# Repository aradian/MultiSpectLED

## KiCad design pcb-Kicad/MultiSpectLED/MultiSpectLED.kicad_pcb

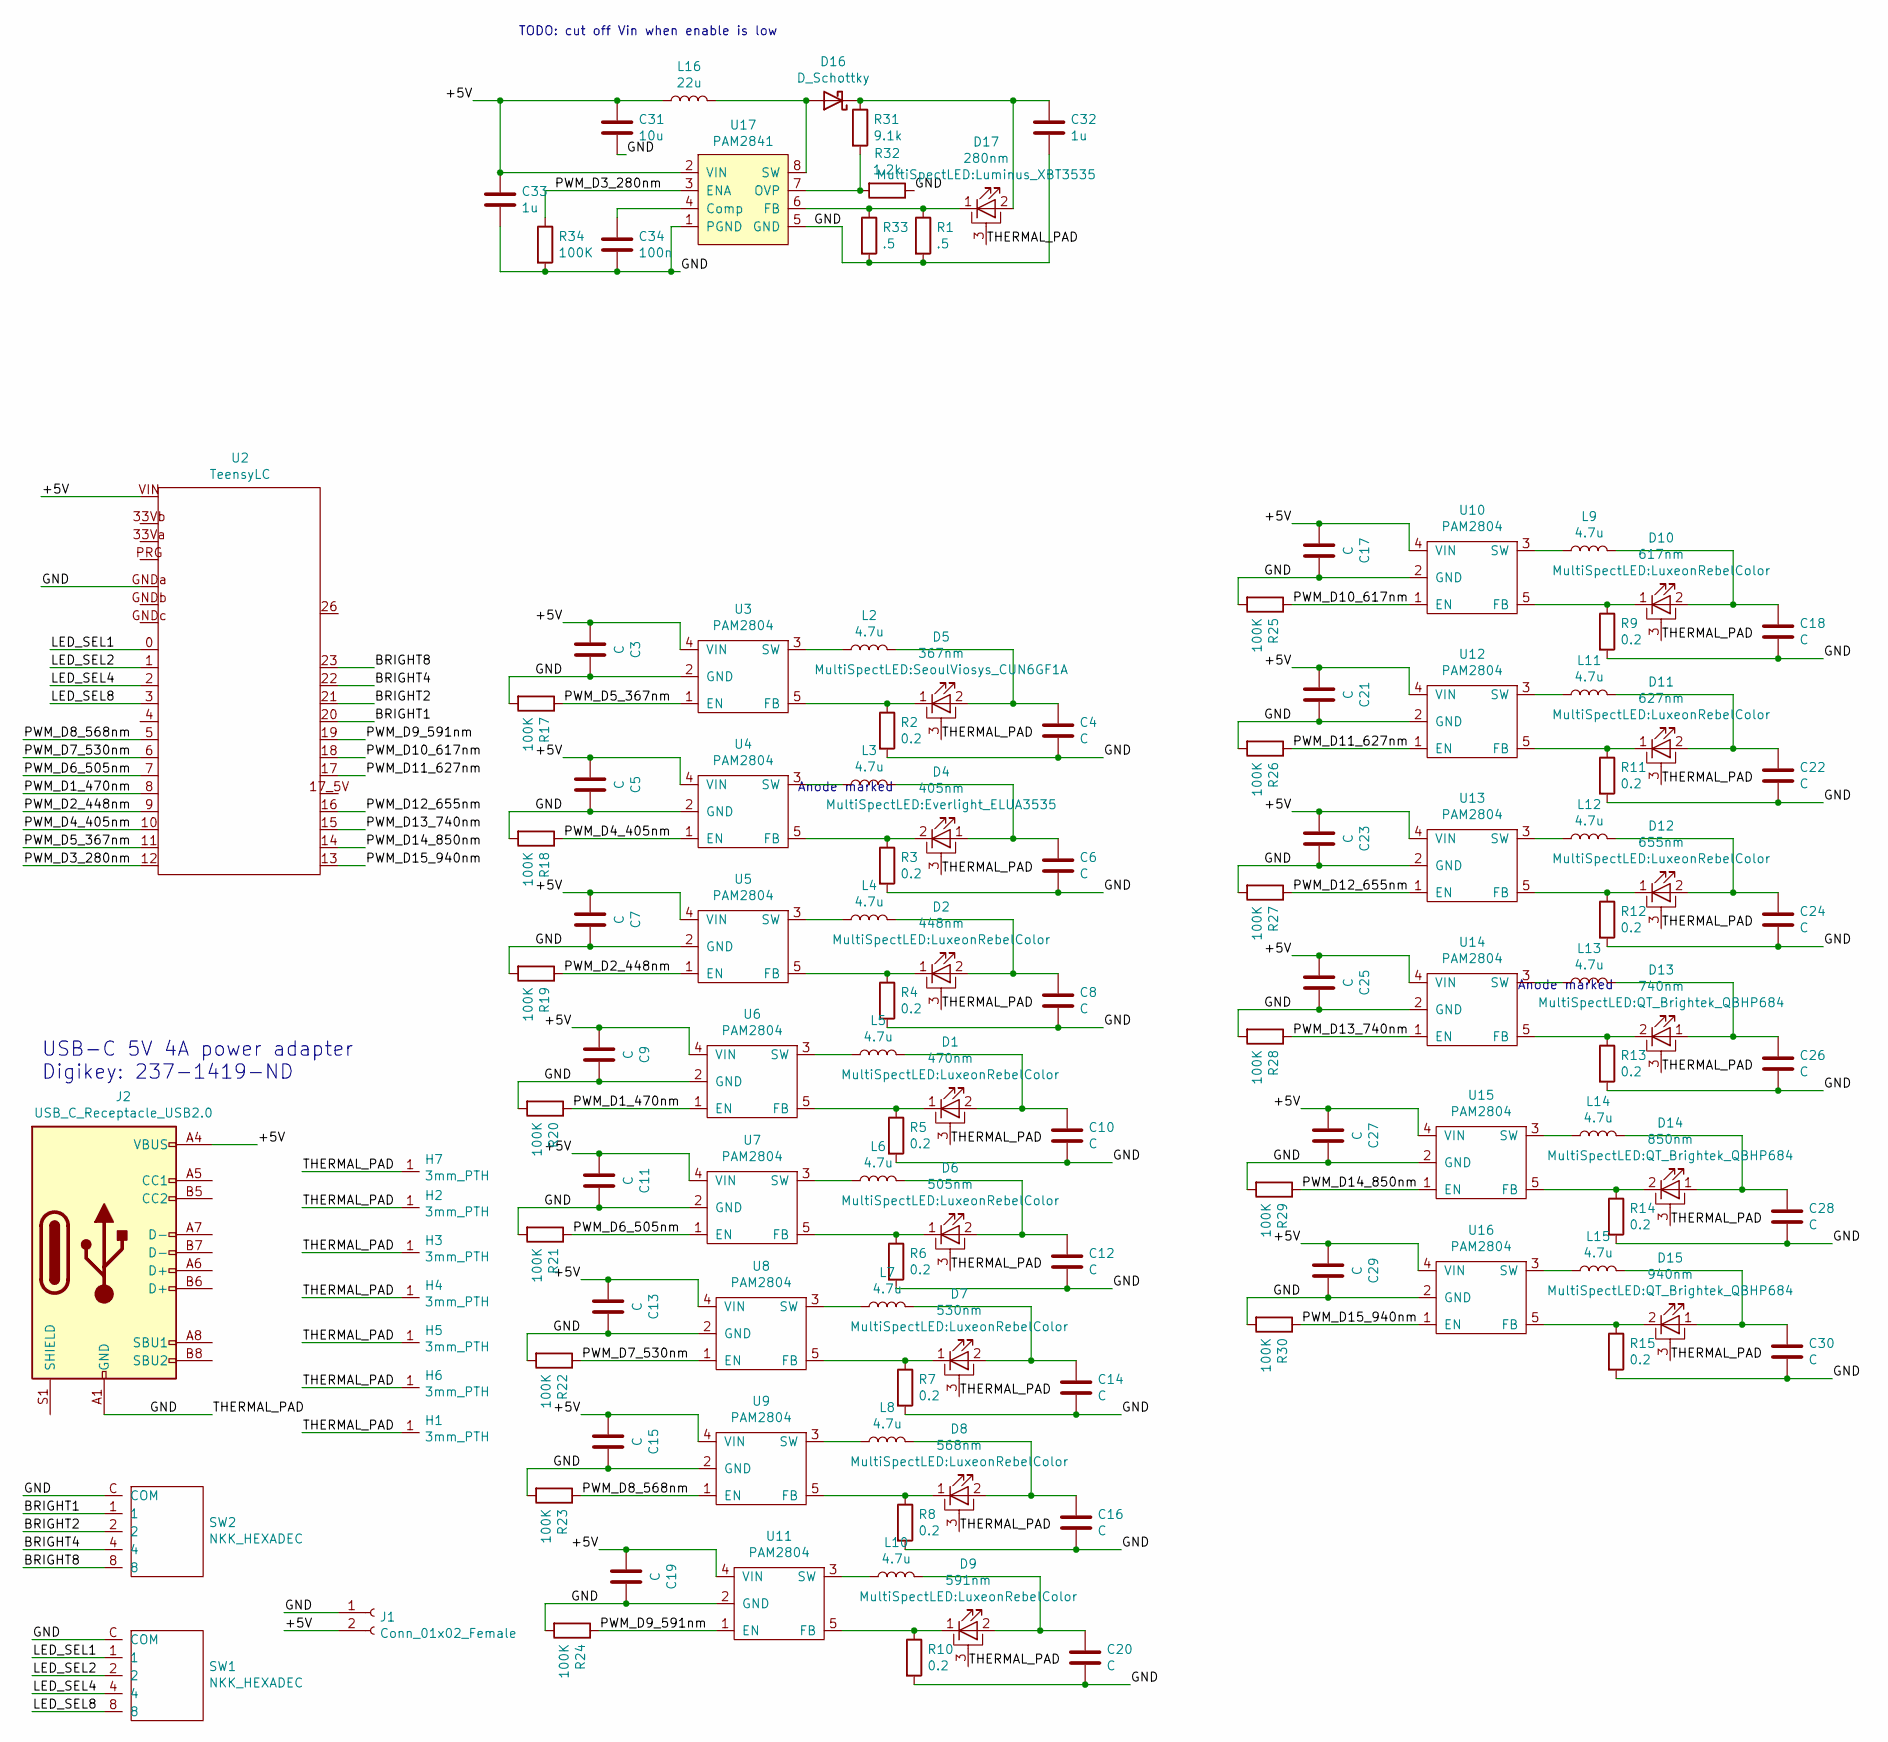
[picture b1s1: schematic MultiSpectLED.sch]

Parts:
C3, C4, C5, C6, C7, C8, C9, C10, C11, C12, C13, C14, C15, C16, C17, C18, C19, C20, C21, C22, C23, C24, C25, C26, C27, C28, C29, C30: C; C_0805_2012Metric; Digikey Part Number 490-3886-1-ND
C31: 10u; C_0805_2012Metric; Digi-Key_PN 1276-2891-1-ND
C32, C33: 1u; C_0805_2012Metric; Digi-Key_PN 1276-1066-1-ND
C34: 100n; C_0402_1005Metric; Digi-Key_PN 1276-1043-1-ND
D1: 470nm; LuxeonRebelColor; Digikey Part Number 1416-1029-1-ND
D2: 448nm; LuxeonRebelColor; Digikey Part Number 1416-1038-1-ND
D4: 405nm; Everlight_ELUA3535; Digikey Part Number 1080-1620-1-ND
D5: 367nm; SeoulViosys_CUN6GF1A; Digikey Part Number 2112-CUN6GF1ACT-ND
D6: 505nm; LuxeonRebelColor; Digikey Part Number 1416-1031-1-ND
D7: 530nm; LuxeonRebelColor; Digikey Part Number 1416-1036-1-ND
D8: 568nm; LuxeonRebelColor; Digikey Part Number 1416-1185-1-ND
D9: 591nm; LuxeonRebelColor; Digikey Part Number 1416-1027-1-ND
D10: 617nm; LuxeonRebelColor; Digikey Part Number 1416-1026-1-ND
D11: 627nm; LuxeonRebelColor; Digikey Part Number 1416-1024-1-ND
D12: 655nm; LuxeonRebelColor; Digikey Part Number 1416-1701-1-ND
D13: 740nm; QT_Brightek_QBHP684; Digikey Part Number 1516-1213-1-ND
D14: 850nm; QT_Brightek_QBHP684
D15: 940nm; QT_Brightek_QBHP684
D16: D_Schottky; D_TUMD2; Digi-Key_PN MSS2P2-M3/89AGICT-ND
D17: 280nm; Luminus_XBT3535; Digikey Part Number 1214-XBT-3535-UV-A130-CD270-00CT-ND
H1, H2, H3, H4, H5, H6, H7: 3mm_PTH
J1: Conn_01x02_Female; FAN_PADS
J2: USB_C_Receptacle_USB2.0; USB_C_Receptacle_Amphenol_12401610E4-2A; Digikey Part Number 12401610E4#2ACT-ND
L2, L3, L4, L5, L6, L7, L8, L9, L10, L11, L12, L13, L14, L15: 4.7u; L_1007_2518Metric; Digikey Part Number 587-1621-1-ND
L16: 22u; L_Taiyo-Yuden_NR-50xx; Digikey Part Number 587-NRS5040T220MMGKCT-ND
R1, R33: .5; R_0603_1608Metric; Digi-Key_PN CSR0603FKR500CT-ND
R2, R3, R4, R5, R6, R7, R8, R9, R10, R11, R12, R13, R14, R15: 0.2; R_0805_2012Metric; Digikey Part Number RL12S.20FCT-ND
R17, R18, R19, R20, R21, R22, R23, R24, R25, R26, R27, R28, R29, R30, R34: 100K; R_0402_1005Metric; Digikey Part Number RC1005F104CS
R31: 9.1k; R_0402_1005Metric; Digi-Key_PN RMCF0402FT9K10CT-ND
R32: 1.2k; R_0402_1005Metric; Digi-Key_PN RMCF0402FT1K20CT-ND
SW1, SW2: NKK_HEXADEC; NKK_FR02; Digikey Part Number 360-2543-1-ND
U2: TeensyLC; Digikey Part Number 1568-1233-ND
U3, U4, U5, U6, U7, U8, U9, U10, U11, U12, U13, U14, U15, U16: PAM2804; SOT-23-5; Digikey Part Number PAM2804AAB010DICT-ND
U17: PAM2841; MSOP-8_3x3mm_P0.65mm

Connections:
/+5V: C3.2, C5.2, C7.2, C9.2, C11.2, C13.2, C15.2, C17.2, C19.2, C21.2, C23.2, C25.2, C27.2, C29.2, C31.2, C33.1, J1.2, J2.A4 (VBUS), J2.A9 (VBUS), J2.B4 (VBUS), J2.B9 (VBUS), L16.1, U2.VIN, U3.4 (VIN), U4.4 (VIN), U5.4 (VIN), U6.4 (VIN), U7.4 (VIN), U8.4 (VIN), U9.4 (VIN), U10.4 (VIN), U11.4 (VIN), U12.4 (VIN), U13.4 (VIN), U14.4 (VIN), U15.4 (VIN), U16.4 (VIN), U17.2 (VIN)
/BRIGHT1: SW2.1, U2.20
/BRIGHT2: SW2.2, U2.21
/BRIGHT4: SW2.4, U2.22
/BRIGHT8: SW2.8, U2.23
/GND: C3.1, C4.2, C5.1, C6.2, C7.1, C8.2, C9.1, C10.2, C11.1, C12.2, C13.1, C14.2, C15.1, C16.2, C17.1, C18.2, C19.1, C20.2, C21.1, C22.2, C23.1, C24.2, C25.1, C26.2, C27.1, C28.2, C29.1, C30.2, C31.1, C32.2, C33.2, C34.2, D1.3 (PAD), D2.3 (PAD), D4.3 (PAD), D5.3 (PAD), D6.3 (PAD), D7.3 (PAD), D8.3 (PAD), D9.3 (PAD), D10.3 (PAD), D11.3 (PAD), D12.3 (PAD), D13.3 (PAD), D14.3 (PAD), D15.3 (PAD), D17.3 (PAD), H1.1, H2.1, H3.1, H4.1, H5.1, H6.1, H7.1, J1.1, J2.A1 (GND), J2.A12 (GND), J2.B1 (GND), J2.B12 (GND), R1.2, R2.2, R3.2, R4.2, R5.2, R6.2, R7.2, R8.2, R9.2, R10.2, R11.2, R12.2, R13.2, R14.2, R15.2, R17.2, R18.2, R19.2, R20.2, R21.2, R22.2, R23.2, R24.2, R25.2, R26.2, R27.2, R28.2, R29.2, R30.2, R32.1, R33.2, R34.2, SW1.C (COM), SW2.C (COM), U2.GNDa, U3.2 (GND), U4.2 (GND), U5.2 (GND), U6.2 (GND), U7.2 (GND), U8.2 (GND), U9.2 (GND), U10.2 (GND), U11.2 (GND), U12.2 (GND), U13.2 (GND), U14.2 (GND), U15.2 (GND), U16.2 (GND), U17.1 (PGND), U17.5 (GND)
/LED_SEL1: SW1.1, U2.0
/LED_SEL2: SW1.2, U2.1
/LED_SEL4: SW1.4, U2.2
/LED_SEL8: SW1.8, U2.3
/PWM_D1_470nm: R20.1, U2.8, U6.1 (EN)
/PWM_D2_448nm: R19.1, U2.9, U5.1 (EN)
/PWM_D3_280nm: R34.1, U2.12, U17.3 (ENA)
/PWM_D4_405nm: R18.1, U2.10, U4.1 (EN)
/PWM_D5_367nm: R17.1, U2.11, U3.1 (EN)
/PWM_D6_505nm: R21.1, U2.7, U7.1 (EN)
/PWM_D7_530nm: R22.1, U2.6, U8.1 (EN)
/PWM_D8_568nm: R23.1, U2.5, U9.1 (EN)
/PWM_D9_591nm: R24.1, U2.19, U11.1 (EN)
/PWM_D10_617nm: R25.1, U2.18, U10.1 (EN)
/PWM_D11_627nm: R26.1, U2.17, U12.1 (EN)
/PWM_D12_655nm: R27.1, U2.16, U13.1 (EN)
/PWM_D13_740nm: R28.1, U2.15, U14.1 (EN)
/PWM_D14_850nm: R29.1, U2.14, U15.1 (EN)
/PWM_D15_940nm: R30.1, U2.13, U16.1 (EN)
unnamed: C4.1, D5.2 (A), L2.2
unnamed: C6.1, D4.1 (A), L3.2
unnamed: C8.1, D2.2 (A), L4.2
unnamed: C10.1, D1.2 (A), L5.2
unnamed: C12.1, D6.2 (A), L6.2
unnamed: C14.1, D7.2 (A), L7.2
unnamed: C16.1, D8.2 (A), L8.2
unnamed: C18.1, D10.2 (A), L9.2
unnamed: C20.1, D9.2 (A), L10.2
unnamed: C22.1, D11.2 (A), L11.2
unnamed: C24.1, D12.2 (A), L12.2
unnamed: C26.1, D13.1 (A), L13.2
unnamed: C28.1, D14.1 (A), L14.2
unnamed: C30.1, D15.1 (A), L15.2
unnamed: C32.1, D16.1 (K), D17.2 (A), R31.1
unnamed: C34.1, U17.4 (Comp)
unnamed: D1.1 (K), R5.1, U6.5 (FB)
unnamed: D2.1 (K), R4.1, U5.5 (FB)
unnamed: D4.2 (K), R3.1, U4.5 (FB)
unnamed: D5.1 (K), R2.1, U3.5 (FB)
unnamed: D6.1 (K), R6.1, U7.5 (FB)
unnamed: D7.1 (K), R7.1, U8.5 (FB)
unnamed: D8.1 (K), R8.1, U9.5 (FB)
unnamed: D9.1 (K), R10.1, U11.5 (FB)
unnamed: D10.1 (K), R9.1, U10.5 (FB)
unnamed: D11.1 (K), R11.1, U12.5 (FB)
unnamed: D12.1 (K), R12.1, U13.5 (FB)
unnamed: D13.2 (K), R13.1, U14.5 (FB)
unnamed: D14.2 (K), R14.1, U15.5 (FB)
unnamed: D15.2 (K), R15.1, U16.5 (FB)
unnamed: D16.2 (A), L16.2, U17.8 (SW)
unnamed: D17.1 (K), R1.1, R33.1, U17.6 (FB)
unnamed: L2.1, U3.3 (SW)
unnamed: L3.1, U4.3 (SW)
unnamed: L4.1, U5.3 (SW)
unnamed: L5.1, U6.3 (SW)
unnamed: L6.1, U7.3 (SW)
unnamed: L7.1, U8.3 (SW)
unnamed: L8.1, U9.3 (SW)
unnamed: L9.1, U10.3 (SW)
unnamed: L10.1, U11.3 (SW)
unnamed: L11.1, U12.3 (SW)
unnamed: L12.1, U13.3 (SW)
unnamed: L13.1, U14.3 (SW)
unnamed: L14.1, U15.3 (SW)
unnamed: L15.1, U16.3 (SW)
unnamed: R31.2, R32.2, U17.7 (OVP)

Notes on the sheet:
Anode marked
USB-C 5V 4A power adapter Digikey: 237-1419-ND
TODO: cut off Vin when enable is low

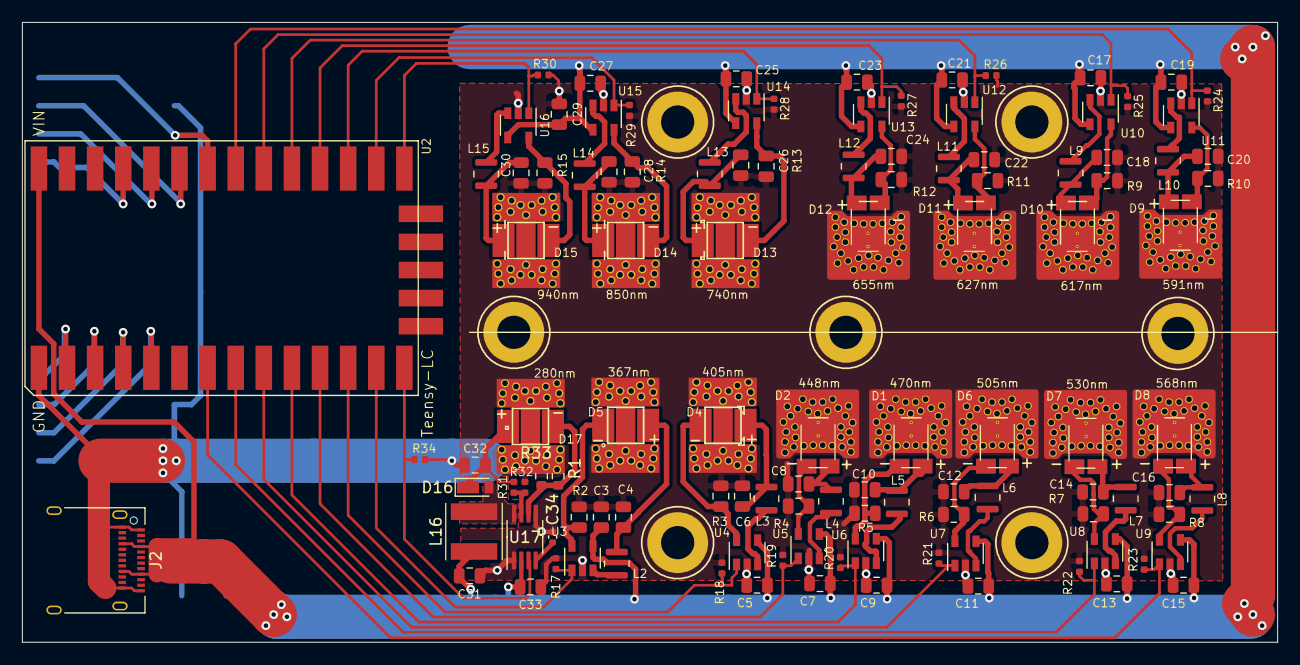
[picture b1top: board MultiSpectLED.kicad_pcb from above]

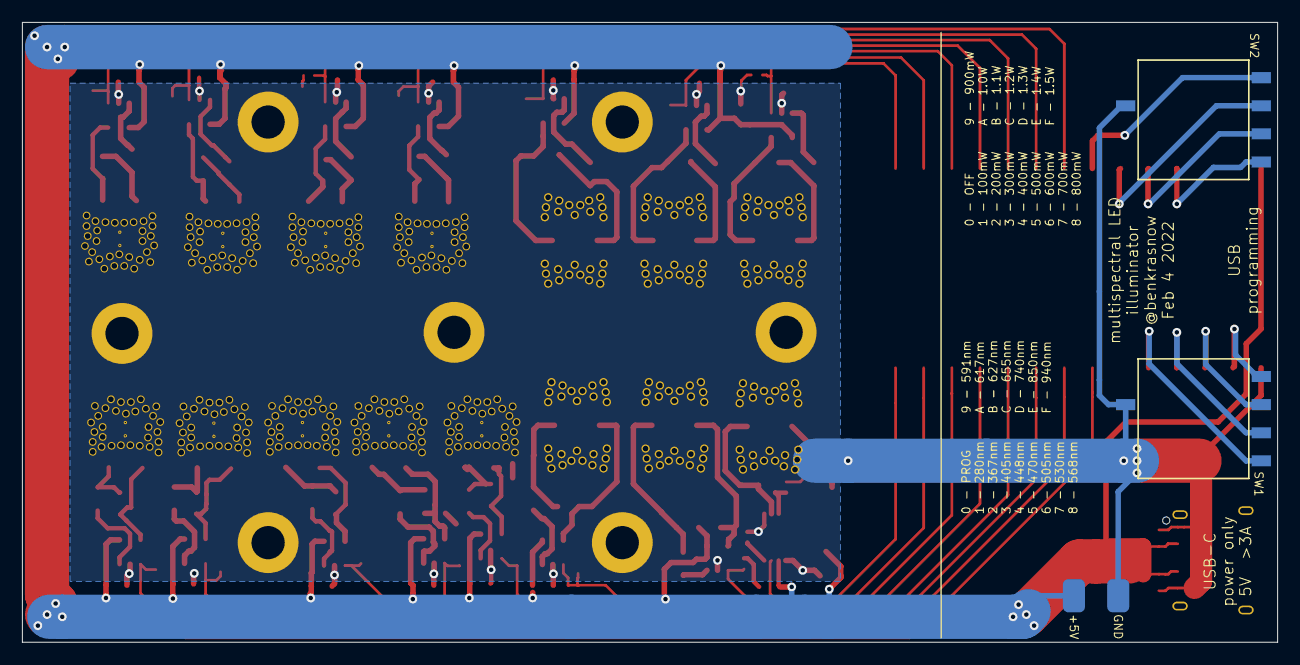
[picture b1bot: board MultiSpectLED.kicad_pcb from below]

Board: 2 copper layers, 113.4 x 56.0 mm, 123 parts (3 on the bottom side), 72 nets.

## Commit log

2022-05-28 Use boost driver for 280nm LED
